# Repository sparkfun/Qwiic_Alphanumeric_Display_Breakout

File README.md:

SparkFun Qwiic Alphanumeric Display
========================================

[*Qwiic Alphanumeric Display - Pink (COM-16919)*](https://www.sparkfun.com/products/16919)

[*Qwiic Alphanumeric Display - Green (COM-18566)*](https://www.sparkfun.com/products/18566)

[*Qwiic Alphanumeric Display - Red (COM-16916)*](https://www.sparkfun.com/products/16916)

[*Qwiic Alphanumeric Display - Blue (COM-16917)*](https://www.sparkfun.com/products/16917)

[*Qwiic Alphanumeric Display - Purple (COM-16918)*](https://www.sparkfun.com/products/16918)

[*Qwiic Alphanumeric Display - White (COM-18565)*](https://www.sparkfun.com/products/18565)

We are quite familiar with seven-segment displays. We see them on our alarm clocks, ovens, and microwaves. By adding more segments to each digit you can display more than just numbers! Introducing the brand new SparkFun Qwiic Alphanumeric Display. These fourteen-segment digits allow you to display all sorts of numbers, characters, and symbols. With [Qwiic](https://www.sparkfun.com/qwiic), simply plug it in and go. No soldering, no figuring out which is SDA or SCL, and no voltage regulation or translation required! 

The [SparkFun Alphanumeric Display Arduino library](https://github.com/sparkfun/SparkFun_Alphanumeric_Display_Arduino_Library) makes printing strings to the display as easy as calling the print() function. With this library, you'll be able to send I<sup>2</sup>C commands to the VK16K33 LED driver chip to light up segments (including the decimal point or colon) and even scroll your string across the display. You can download the library through the Arduino library manager by searching 'SparkFun Alphanumeric Display' or you can get the GitHub repo as a .zip file and install the library from there.

The VK16K33 also supports I<sup>2</sup>C address configuration. Simply close a combination of the address jumpers on the back and you can communicate with up to four displays on the same bus. Our slim board design also features detachable standoff holes, vertical Qwiic connectors, and internal mounting holes.

SparkFun labored with love to design this board. Feel like supporting open source hardware? 
Buy a [board]() from SparkFun!

Repository Contents
-------------------

* **/Documents** - Data sheet for the LED Driver and Alphanumeric Displays (Blue and Red)
* **/Hardware** - Eagle design files (.brd, .sch)
* **/Production** - Production panel files (.brd) within the Production folder

Documentation
--------------
* **[Library](https://github.com/sparkfun/SparkFun_Alphanumeric_Display_Arduino_Library)** - <LANGUAGE> library for the Qwiic Alphanumeric Display Breakout.
* **[Hookup Guide](https://learn.sparkfun.com/tutorials/sparkfun-qwiic-alphanumeric-display-hookup-guide)** - Basic hookup guide for the Qwiic Alphanumeric Display Breakout.

License Information
-------------------

This product is _**open source**_! 

Please review the LICENSE.md file for license information. 

If you have any questions or concerns on licensing, please contact technical support on our [SparkFun forums](https://forum.sparkfun.com/viewforum.php?f=152).

Distributed as-is; no warranty is given.

- Your friends at SparkFun.

_<COLLABORATION CREDIT>_

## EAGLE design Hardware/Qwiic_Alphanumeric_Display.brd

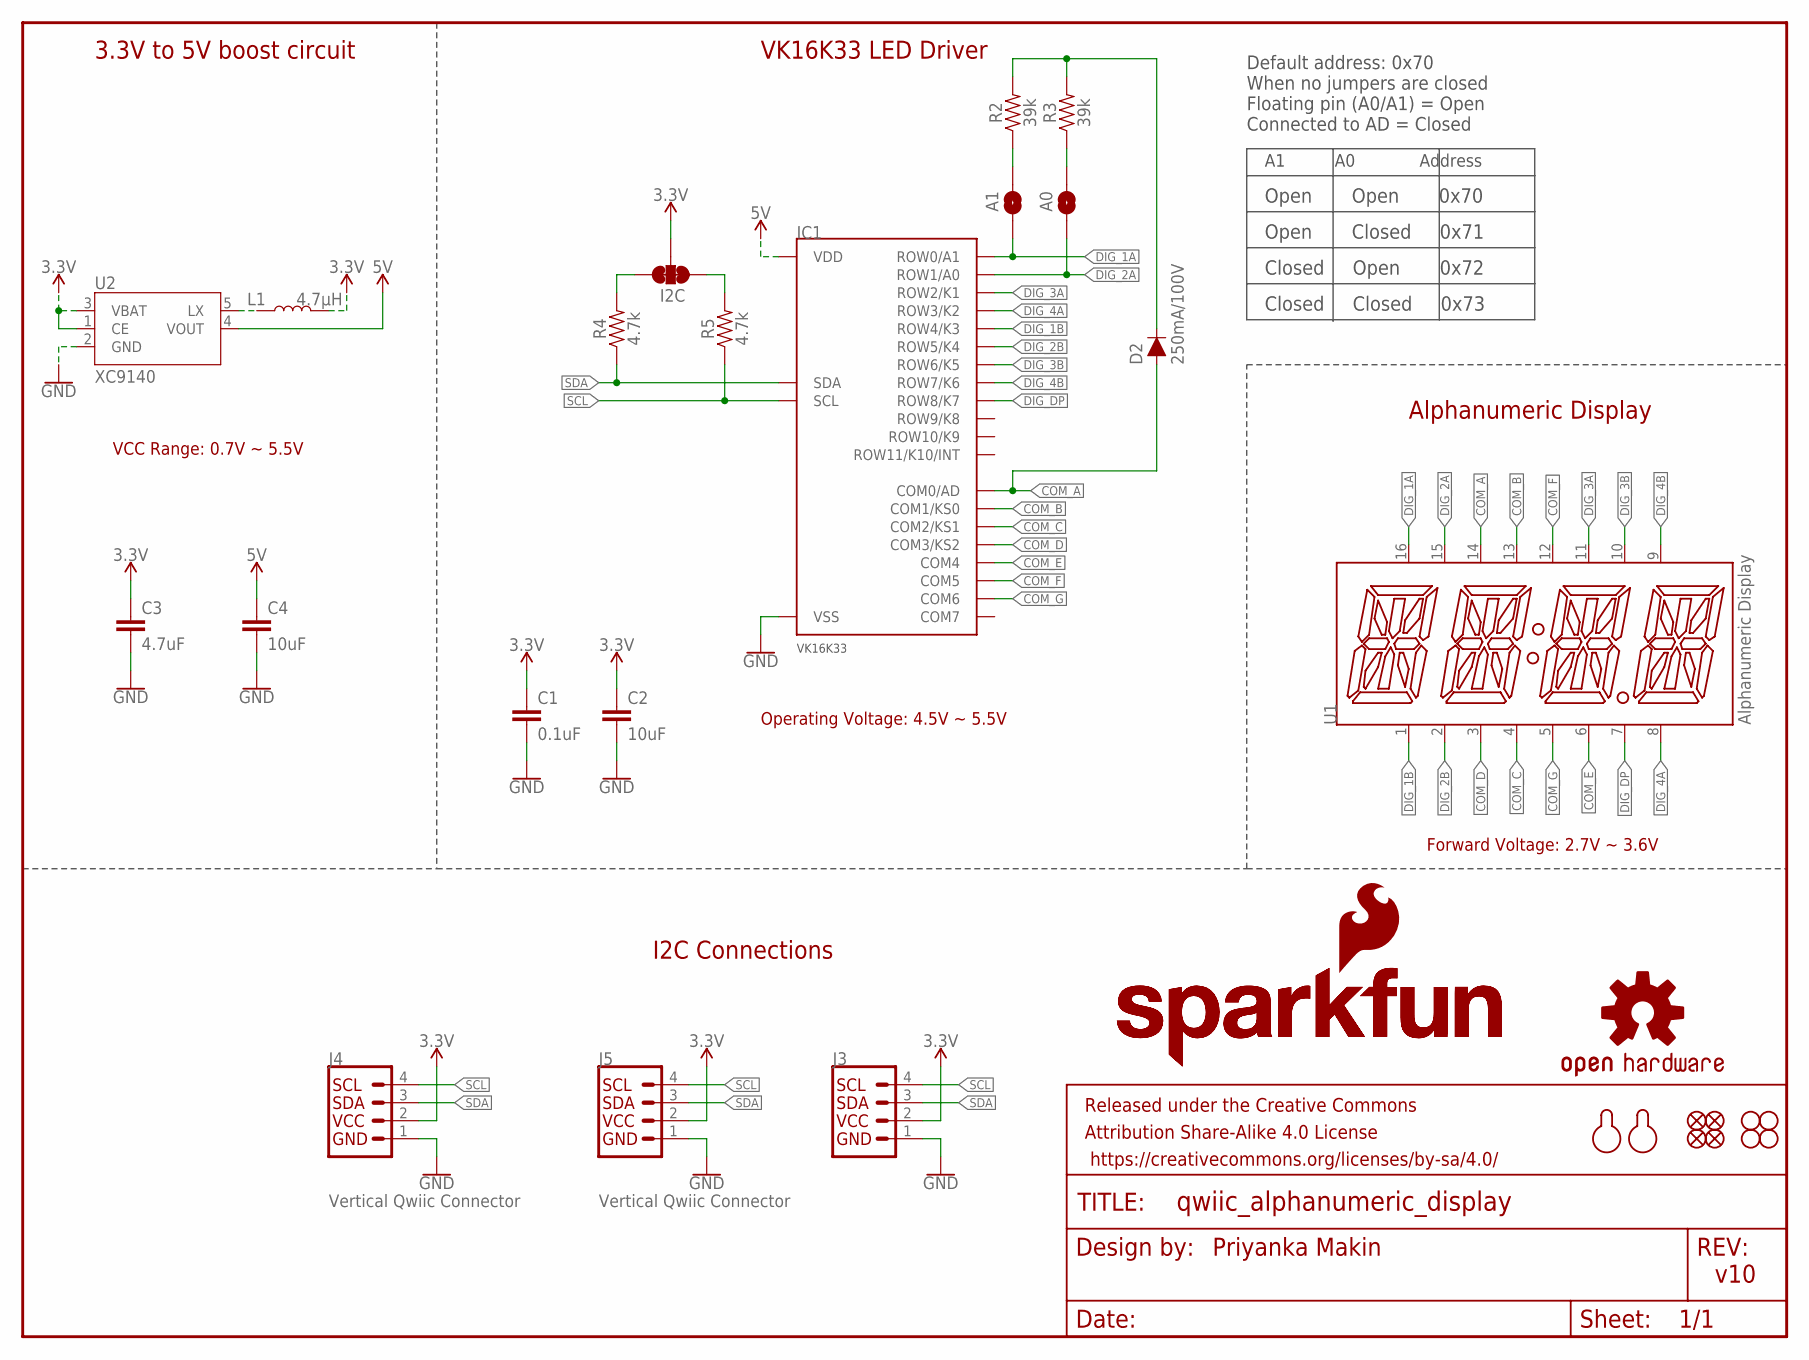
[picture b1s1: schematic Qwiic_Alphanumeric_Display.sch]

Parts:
A0, A1: JUMPER-SMT_2_NO_SILK; SMT-JUMPER_2_NO_SILK
C1: 0.1uF; 0603
C2, C4: 10uF; 0603
C3: 4.7uF; 0603
D2: 250mA/100V; SOD-323
FD1, FD2, FD3, FD4: FIDUCIAL1X2; FIDUCIAL-1X2
FRAME1: FRAME-LETTER; CREATIVE_COMMONS
H1, H2, H3, H4: STAND-OFF
I2C: JUMPER-SMT_3_2-NC_TRACE_NO-SILK; SMT-JUMPER_3_2-NC_TRACE_NO-SILK
IC1: VK16K33VK16K33; VK16K33
J3: I2C_STANDARD_NO_SILK; 1X04_NO_SILK
J4, J5: Vertical Qwiic Connector; JST04_1MM_VERT
L1: 4.7µH; INDUCTOR_4.7UH
LOGO1: OSHW-LOGOMINI; OSHW-LOGO-MINI
LOGO2, LOGO3: SFE_LOGO_NAME.1_INCH; SFE_LOGO_NAME_.1
LOGO4: SFE_LOGO_FLAME.1_INCH; SFE_LOGO_FLAME_.1
R2, R3: 39k; 0603
R4, R5: 4.7k; 0402-TIGHT
U1: Alphanumeric Display; SILSMART_DISPLAY
U2: XC9140; SOT23-5
U$3, U$7: MOUNTING_HOLE_M2-0.4X6

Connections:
3.3V: C1.1, C2.1, C3.1, I2C.2, J3.2, J4.2, J5.2, L1.P$2 (2), U2.1 (CE), U2.3 (VBAT)
5V: C4.1, IC1.24 (VDD), U2.4 (VOUT)
COM_A: D2.A, IC1.2 (COM0/AD), U1.14 (COM_A)
COM_B: IC1.3 (COM1/KS0), U1.13 (COM_B)
COM_C: IC1.4 (COM2/KS1), U1.4 (COM_C)
COM_D: IC1.5 (COM3/KS2), U1.3 (COM_D)
COM_E: IC1.6 (COM4), U1.6 (COM_E)
COM_F: IC1.7 (COM5), U1.12 (COM_F)
COM_G: IC1.8 (COM6), U1.5 (COM_G1)
DIG_1A: A1.1, IC1.21 (ROW0/A1), U1.16 (DIG_1A)
DIG_1B: IC1.17 (ROW4/K3), U1.1 (DIG_1B)
DIG_2A: A0.1, IC1.20 (ROW1/A0), U1.15 (DIG_2A)
DIG_2B: IC1.16 (ROW5/K4), U1.2 (DIG_2B)
DIG_3A: IC1.19 (ROW2/K1), U1.11 (DIG_3A)
DIG_3B: IC1.15 (ROW6/K5), U1.10 (DIG_3B)
DIG_4A: IC1.18 (ROW3/K2), U1.8 (DIG_4A)
DIG_4B: IC1.14 (ROW7/K6), U1.9 (DIG_4B)
DIG_DP: IC1.13 (ROW8/K7), U1.7 (DIG_DP)
GND: C1.2, C2.2, C3.2, C4.2, IC1.1 (VSS), J3.1, J4.1, J5.1, U2.2 (GND)
unnamed: I2C.3, R4.2
unnamed: A1.2, R2.1
unnamed: A0.2, R3.1
unnamed: I2C.1, R5.2
unnamed: D2.C, R2.2, R3.2
unnamed: L1.P$1 (1), U2.5 (LX)
SCL: IC1.22 (SCL), J3.4, J4.4, J5.4, R5.1
SDA: IC1.23 (SDA), J3.3, J4.3, J5.3, R4.1

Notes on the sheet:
Priyanka Makin
I2C Connections
A1 A0 Address
Default address: 0x70 When no jumpers are closed Floating pin (A0/A1) = Open Connected to AD = Closed
v10
Alphanumeric Display
VK16K33 LED Driver
3.3V to 5V boost circuit
VK16K33
VCC Range: 0.7V ~ 5.5V
Operating Voltage: 4.5V ~ 5.5V
Forward Voltage: 2.7V ~ 3.6V
Open Closed 0x71
Open Open 0x70
Closed Open 0x72
Closed Closed 0x73

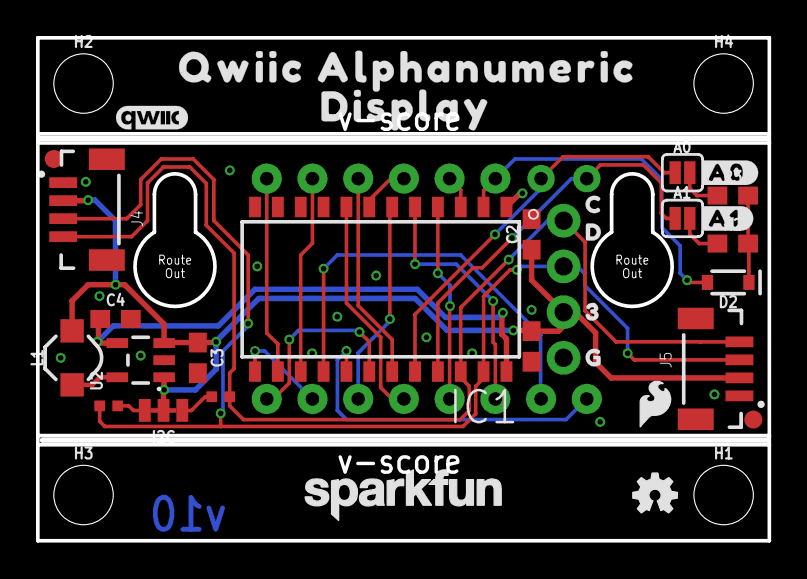
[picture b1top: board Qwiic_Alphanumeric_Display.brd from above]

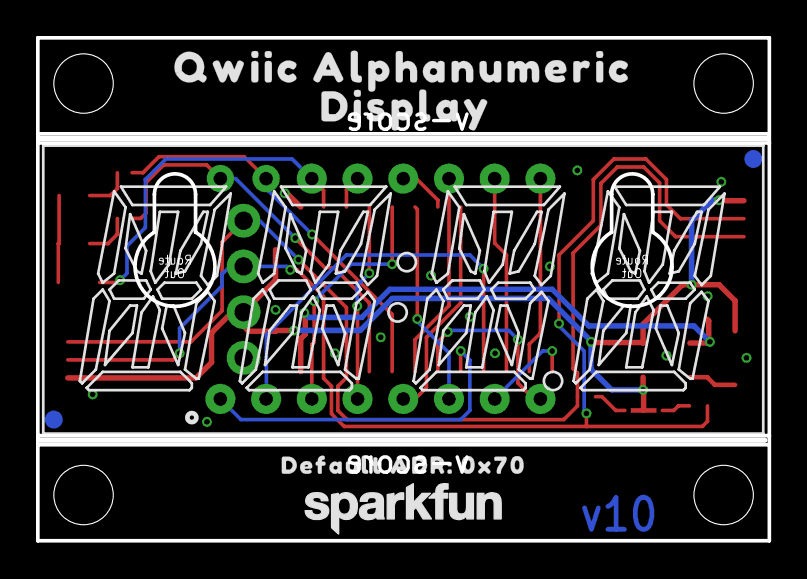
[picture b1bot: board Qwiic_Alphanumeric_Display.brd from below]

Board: 2 copper layers, 40.6 x 27.9 mm, 46 parts (7 on the bottom side), 27 nets.

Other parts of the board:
U$1: DEFAULT_ADR#_0X700
U$6: QWIIC_4MM
U$8, U$9: QWIIC_ALPHANUMERIC0
U$10, U$11: DISPLAY0
U$12: #A0#0
U$13: #A1#0
U$14: C0
U$15: D0
U$16: 30
U$17: G0

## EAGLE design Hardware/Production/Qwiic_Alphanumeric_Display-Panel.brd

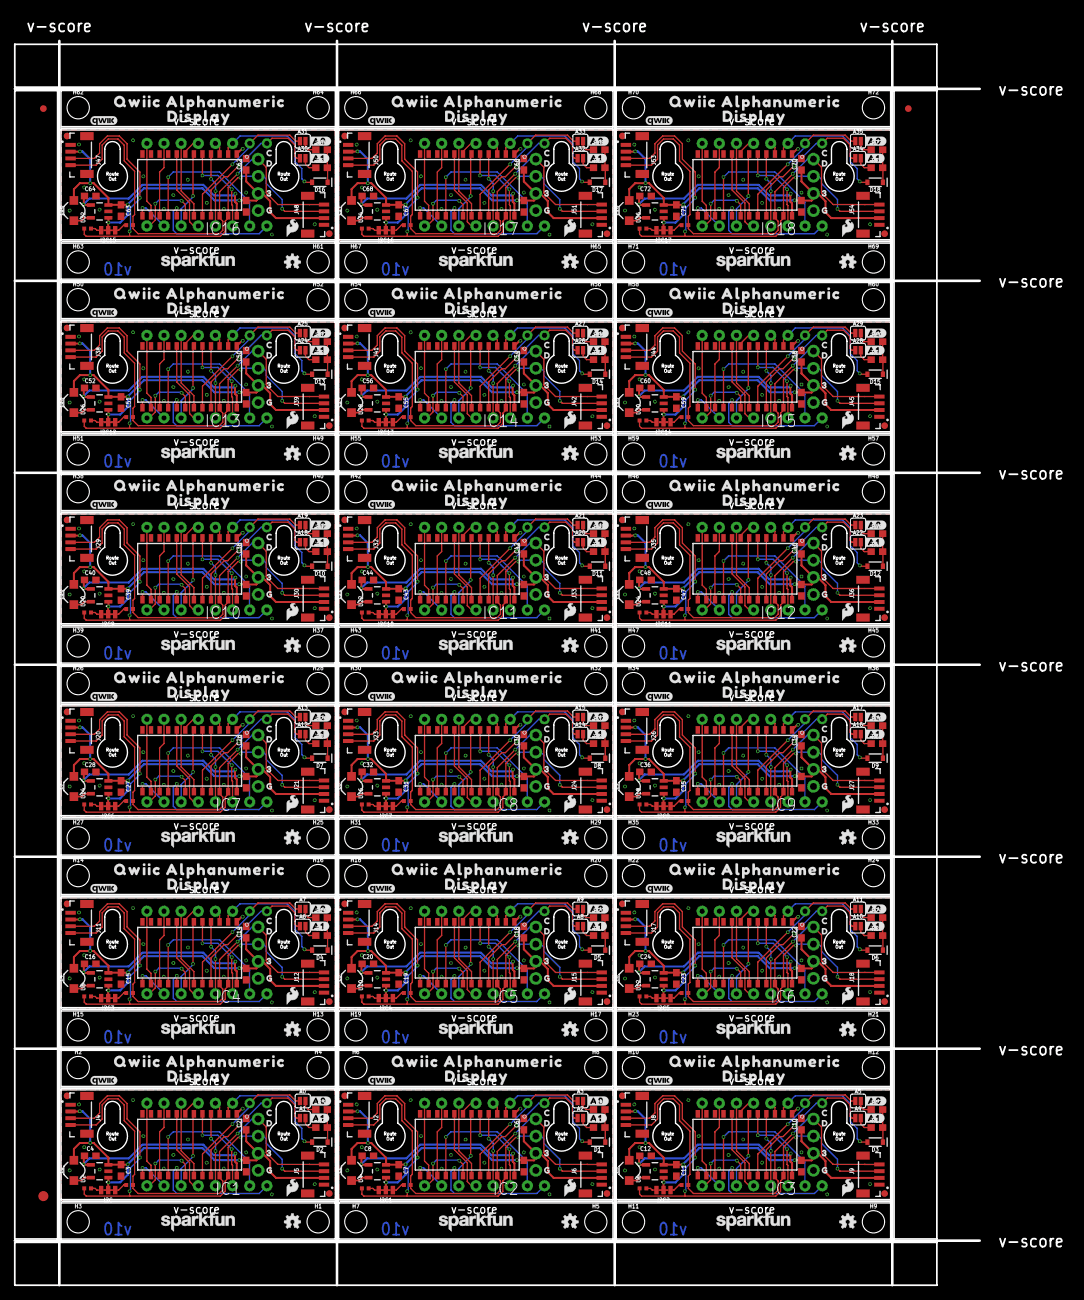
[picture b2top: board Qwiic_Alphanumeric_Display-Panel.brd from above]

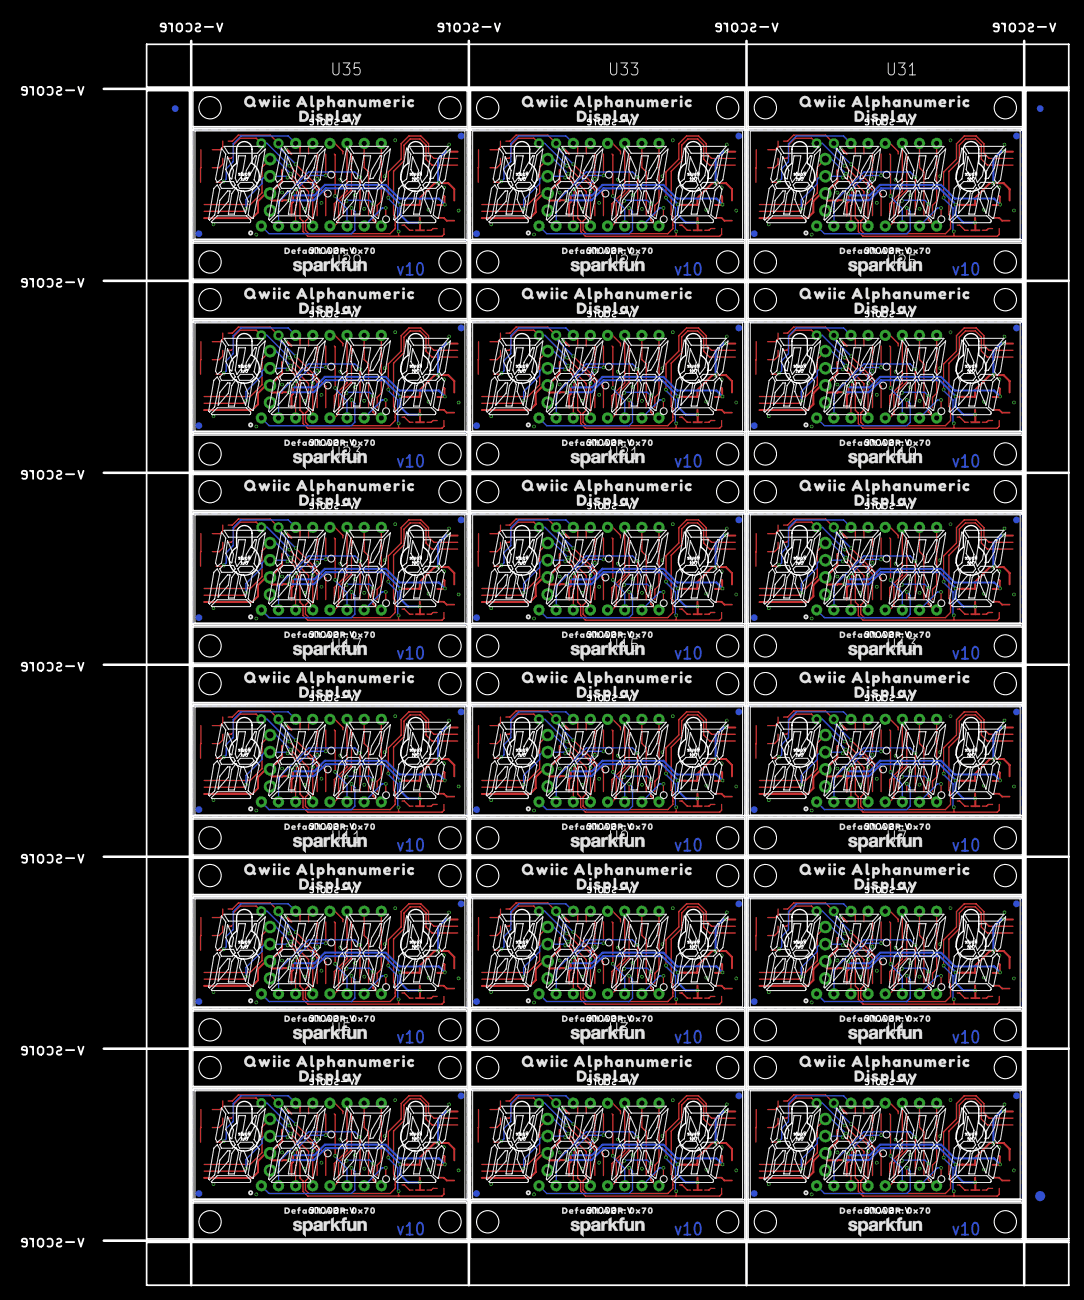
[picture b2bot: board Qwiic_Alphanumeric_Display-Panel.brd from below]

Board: 2 copper layers, 143.0 x 184.4 mm, 816 parts (129 on the bottom side), 486 nets.

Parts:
A0, A1, A2, A3, A4, A5, A6, A7, A8, A9, A10, A11, A12, A13, A14, A15, A16, A17, A18, A19, A20, A21, A22, A23, A24, A25, A26, A27, A28, A29, A30, A31, A32, A33, A34, A35: JUMPER-SMT_2_NO_SILK; SMT-JUMPER_2_NO_SILK
C1, C5, C9, C13, C17, C21, C25, C29, C33, C37, C41, C45, C49, C53, C57, C61, C65, C69: 0.1uF; 0603
C2, C4, C6, C8, C10, C12, C14, C16, C18, C20, C22, C24, C26, C28, C30, C32, C34, C36, C38, C40, C42, C44, C46, C48, C50, C52, C54, C56, C58, C60, C62, C64, C66, C68, C70, C72: 10uF; 0603
C3, C7, C11, C15, C19, C23, C27, C31, C35, C39, C43, C47, C51, C55, C59, C63, C67, C71: 4.7uF; 0603
D1, D2, D3, D4, D5, D6, D7, D8, D9, D10, D11, D12, D13, D14, D15, D16, D17, D18: 250mA/100V; SOD-323
E$1, E$2, E$3, E$4: FIDUCIAL-1X2
E$5, E$6: FIDUCIAL-1.5X3
FD1, FD2, FD3, FD4, FD5, FD6, FD7, FD8, FD9, FD10, FD11, FD12, FD13, FD14, FD15, FD16, FD17, FD18, FD19, FD20, FD21, FD22, FD23, FD24, FD25, FD26, FD27, FD28, FD29, FD30, FD31, FD32, FD33, FD34, FD35, FD36, FD37, FD38, FD39, FD40, FD41, FD42, FD43, FD44, FD45, FD46, FD47, FD48, FD49, FD50, FD51, FD52, FD53, FD54, FD55, FD56, FD57, FD58, FD59, FD60, FD61, FD62, FD63, FD64, FD65, FD66, FD67, FD68, FD69, FD70, FD71, FD72: FIDUCIAL1X2; FIDUCIAL-1X2
H1, H2, H3, H4, H5, H6, H7, H8, H9, H10, H11, H12, H13, H14, H15, H16, H17, H18, H19, H20, H21, H22, H23, H24, H25, H26, H27, H28, H29, H30, H31, H32, H33, H34, H35, H36, H37, H38, H39, H40, H41, H42, H43, H44, H45, H46, H47, H48, H49, H50, H51, H52, H53, H54, H55, H56, H57, H58, H59, H60, H61, H62, H63, H64, H65, H66, H67, H68, H69, H70, H71, H72: STAND-OFF
I2C, I2C1, I2C2, I2C3, I2C4, I2C5, I2C6, I2C7, I2C8, I2C9, I2C10, I2C11, I2C12, I2C13, I2C14, I2C15, I2C16, I2C17: JUMPER-SMT_3_2-NC_TRACE_NO-SILK; SMT-JUMPER_3_2-NC_TRACE_NO-SILK
IC1, IC2, IC3, IC4, IC5, IC6, IC7, IC8, IC9, IC10, IC11, IC12, IC13, IC14, IC15, IC16, IC17, IC18: VK16K33
J1, J3, J7, J10, J13, J16, J19, J22, J25, J28, J31, J34, J37, J40, J43, J46, J49, J52: 1X04_NO_SILK
J2, J4, J5, J6, J8, J9, J11, J12, J14, J15, J17, J18, J20, J21, J23, J24, J26, J27, J29, J30, J32, J33, J35, J36, J38, J39, J41, J42, J44, J45, J47, J48, J50, J51, J53, J54: Vertical Qwiic Connector; JST04_1MM_VERT
L1, L2, L3, L4, L5, L6, L7, L8, L9, L10, L11, L12, L13, L14, L15, L16, L17, L18: 4.7µH; INDUCTOR_4.7UH
LOGO1, LOGO5, LOGO9, LOGO13, LOGO17, LOGO21, LOGO25, LOGO29, LOGO33, LOGO37, LOGO41, LOGO45, LOGO49, LOGO53, LOGO57, LOGO61, LOGO65, LOGO69: OSHW-LOGOMINI; OSHW-LOGO-MINI
LOGO2, LOGO3, LOGO6, LOGO7, LOGO10, LOGO11, LOGO14, LOGO15, LOGO18, LOGO19, LOGO22, LOGO23, LOGO26, LOGO27, LOGO30, LOGO31, LOGO34, LOGO35, LOGO38, LOGO39, LOGO42, LOGO43, LOGO46, LOGO47, LOGO50, LOGO51, LOGO54, LOGO55, LOGO58, LOGO59, LOGO62, LOGO63, LOGO66, LOGO67, LOGO70, LOGO71: SFE_LOGO_NAME.1_INCH; SFE_LOGO_NAME_.1
LOGO4, LOGO8, LOGO12, LOGO16, LOGO20, LOGO24, LOGO28, LOGO32, LOGO36, LOGO40, LOGO44, LOGO48, LOGO52, LOGO56, LOGO60, LOGO64, LOGO68, LOGO72: SFE_LOGO_FLAME.1_INCH; SFE_LOGO_FLAME_.1
R1, R4, R5, R6, R9, R10, R13, R14, R17, R18, R21, R22, R25, R26, R29, R30, R33, R34, R37, R38, R41, R42, R45, R46, R49, R50, R53, R54, R57, R58, R61, R62, R65, R66, R69, R70: 4.7k; 0402-TIGHT
R2, R3, R7, R8, R11, R12, R15, R16, R19, R20, R23, R24, R27, R28, R31, R32, R35, R36, R39, R40, R43, R44, R47, R48, R51, R52, R55, R56, R59, R60, R63, R64, R67, R68, R71, R72: 39k; 0603
U1, U3, U5, U7, U9, U11, U13, U15, U17, U19, U21, U23, U25, U27, U29, U31, U33, U35: Alphanumeric Display; SILSMART_DISPLAY
U2, U4, U6, U8, U10, U12, U14, U16, U18, U20, U22, U24, U26, U28, U30, U32, U34, U36: XC9140; SOT23-5
U$1, U$28, U$42, U$56, U$70, U$84, U$98, U$112, U$126, U$140, U$154, U$168, U$182, U$196, U$210, U$224, U$238, U$252: DEFAULT_ADR#_0X700
U$2, U$6, U$29, U$43, U$57, U$71, U$85, U$99, U$113, U$127, U$141, U$155, U$169, U$183, U$197, U$211, U$225, U$239: QWIIC_4MM
U$3, U$4, U$5, U$7, U$30, U$31, U$44, U$45, U$58, U$59, U$72, U$73, U$86, U$87, U$100, U$101, U$114, U$115, U$128, U$129, U$142, U$143, U$156, U$157, U$170, U$171, U$184, U$185, U$198, U$199, U$212, U$213, U$226, U$227, U$240, U$241: MOUNTING_HOLE_M2-0.4X6
U$8, U$9, U$18, U$19, U$32, U$33, U$46, U$47, U$60, U$61, U$74, U$75, U$88, U$89, U$102, U$103, U$116, U$117, U$130, U$131, U$144, U$145, U$158, U$159, U$172, U$173, U$186, U$187, U$200, U$201, U$214, U$215, U$228, U$229, U$242, U$243: QWIIC_ALPHANUMERIC0
U$10, U$11, U$20, U$21, U$34, U$35, U$48, U$49, U$62, U$63, U$76, U$77, U$90, U$91, U$104, U$105, U$118, U$119, U$132, U$133, U$146, U$147, U$160, U$161, U$174, U$175, U$188, U$189, U$202, U$203, U$216, U$217, U$230, U$231, U$244, U$245: DISPLAY0
U$12, U$22, U$36, U$50, U$64, U$78, U$92, U$106, U$120, U$134, U$148, U$162, U$176, U$190, U$204, U$218, U$232, U$246: #A0#0
U$13, U$23, U$37, U$51, U$65, U$79, U$93, U$107, U$121, U$135, U$149, U$163, U$177, U$191, U$205, U$219, U$233, U$247: #A1#0
U$14, U$24, U$38, U$52, U$66, U$80, U$94, U$108, U$122, U$136, U$150, U$164, U$178, U$192, U$206, U$220, U$234, U$248: C0
U$15, U$25, U$39, U$53, U$67, U$81, U$95, U$109, U$123, U$137, U$151, U$165, U$179, U$193, U$207, U$221, U$235, U$249: D0
U$16, U$26, U$40, U$54, U$68, U$82, U$96, U$110, U$124, U$138, U$152, U$166, U$180, U$194, U$208, U$222, U$236, U$250: 30
U$17, U$27, U$41, U$55, U$69, U$83, U$97, U$111, U$125, U$139, U$153, U$167, U$181, U$195, U$209, U$223, U$237, U$251: G0

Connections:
3.3V: C1.1, C2.1, C3.1, I2C.2, J3.2, J4.2, J5.2, L1.P$2, U2.1, U2.3
3.3V1: C5.1, C6.1, C7.1, I2C1.2, J1.2, J2.2, J6.2, L2.P$2, U4.1, U4.3
3.3V2: C9.1, C10.1, C11.1, I2C2.2, J7.2, J8.2, J9.2, L3.P$2, U6.1, U6.3
3.3V3: C13.1, C14.1, C15.1, I2C3.2, J10.2, J11.2, J12.2, L4.P$2, U8.1, U8.3
3.3V4: C17.1, C18.1, C19.1, I2C4.2, J13.2, J14.2, J15.2, L5.P$2, U10.1, U10.3
3.3V5: C21.1, C22.1, C23.1, I2C5.2, J16.2, J17.2, J18.2, L6.P$2, U12.1, U12.3
3.3V6: C25.1, C26.1, C27.1, I2C6.2, J19.2, J20.2, J21.2, L7.P$2, U14.1, U14.3
3.3V7: C29.1, C30.1, C31.1, I2C7.2, J22.2, J23.2, J24.2, L8.P$2, U16.1, U16.3
3.3V8: C33.1, C34.1, C35.1, I2C8.2, J25.2, J26.2, J27.2, L9.P$2, U18.1, U18.3
3.3V9: C37.1, C38.1, C39.1, I2C9.2, J28.2, J29.2, J30.2, L10.P$2, U20.1, U20.3
3.3V10: C41.1, C42.1, C43.1, I2C10.2, J31.2, J32.2, J33.2, L11.P$2, U22.1, U22.3
3.3V11: C45.1, C46.1, C47.1, I2C11.2, J34.2, J35.2, J36.2, L12.P$2, U24.1, U24.3
3.3V12: C49.1, C50.1, C51.1, I2C12.2, J37.2, J38.2, J39.2, L13.P$2, U26.1, U26.3
3.3V13: C53.1, C54.1, C55.1, I2C13.2, J40.2, J41.2, J42.2, L14.P$2, U28.1, U28.3
3.3V14: C57.1, C58.1, C59.1, I2C14.2, J43.2, J44.2, J45.2, L15.P$2, U30.1, U30.3
3.3V15: C61.1, C62.1, C63.1, I2C15.2, J46.2, J47.2, J48.2, L16.P$2, U32.1, U32.3
3.3V16: C65.1, C66.1, C67.1, I2C16.2, J49.2, J50.2, J51.2, L17.P$2, U34.1, U34.3
3.3V17: C69.1, C70.1, C71.1, I2C17.2, J52.2, J53.2, J54.2, L18.P$2, U36.1, U36.3
5V: C4.1, IC1.24, U2.4
5V1: C8.1, IC2.24, U4.4
5V2: C12.1, IC3.24, U6.4
5V3: C16.1, IC4.24, U8.4
5V4: C20.1, IC5.24, U10.4
5V5: C24.1, IC6.24, U12.4
5V6: C28.1, IC7.24, U14.4
5V7: C32.1, IC8.24, U16.4
5V8: C36.1, IC9.24, U18.4
5V9: C40.1, IC10.24, U20.4
5V10: C44.1, IC11.24, U22.4
5V11: C48.1, IC12.24, U24.4
5V12: C52.1, IC13.24, U26.4
5V13: C56.1, IC14.24, U28.4
5V14: C60.1, IC15.24, U30.4
5V15: C64.1, IC16.24, U32.4
5V16: C68.1, IC17.24, U34.4
5V17: C72.1, IC18.24, U36.4
COM_A: D2.A, IC1.2, U1.14
COM_A1: D1.A, IC2.2, U3.14
COM_A2: D3.A, IC3.2, U5.14
COM_A3: D4.A, IC4.2, U7.14
COM_A4: D5.A, IC5.2, U9.14
COM_A5: D6.A, IC6.2, U11.14
COM_A6: D7.A, IC7.2, U13.14
COM_A7: D8.A, IC8.2, U15.14
COM_A8: D9.A, IC9.2, U17.14
COM_A9: D10.A, IC10.2, U19.14
COM_A10: D11.A, IC11.2, U21.14
COM_A11: D12.A, IC12.2, U23.14
COM_A12: D13.A, IC13.2, U25.14
COM_A13: D14.A, IC14.2, U27.14
COM_A14: D15.A, IC15.2, U29.14
COM_A15: D16.A, IC16.2, U31.14
COM_A16: D17.A, IC17.2, U33.14
COM_A17: D18.A, IC18.2, U35.14
COM_B: IC1.3, U1.13
COM_B1: IC2.3, U3.13
COM_B2: IC3.3, U5.13
COM_B3: IC4.3, U7.13
COM_B4: IC5.3, U9.13
COM_B5: IC6.3, U11.13
COM_B6: IC7.3, U13.13
COM_B7: IC8.3, U15.13
COM_B8: IC9.3, U17.13
COM_B9: IC10.3, U19.13
COM_B10: IC11.3, U21.13
COM_B11: IC12.3, U23.13
COM_B12: IC13.3, U25.13
COM_B13: IC14.3, U27.13
COM_B14: IC15.3, U29.13
COM_B15: IC16.3, U31.13
COM_B16: IC17.3, U33.13
COM_B17: IC18.3, U35.13
COM_C: IC1.4, U1.4
COM_C1: IC2.4, U3.4
COM_C2: IC3.4, U5.4
COM_C3: IC4.4, U7.4
COM_C4: IC5.4, U9.4
COM_C5: IC6.4, U11.4
COM_C6: IC7.4, U13.4
COM_C7: IC8.4, U15.4
COM_C8: IC9.4, U17.4
COM_C9: IC10.4, U19.4
COM_C10: IC11.4, U21.4
COM_C11: IC12.4, U23.4
COM_C12: IC13.4, U25.4
COM_C13: IC14.4, U27.4
COM_C14: IC15.4, U29.4
COM_C15: IC16.4, U31.4
COM_C16: IC17.4, U33.4
COM_C17: IC18.4, U35.4
COM_D: IC1.5, U1.3
COM_D1: IC2.5, U3.3
COM_D2: IC3.5, U5.3
COM_D3: IC4.5, U7.3
COM_D4: IC5.5, U9.3
COM_D5: IC6.5, U11.3
COM_D6: IC7.5, U13.3
COM_D7: IC8.5, U15.3
COM_D8: IC9.5, U17.3
COM_D9: IC10.5, U19.3
COM_D10: IC11.5, U21.3
COM_D11: IC12.5, U23.3
COM_D12: IC13.5, U25.3
COM_D13: IC14.5, U27.3
COM_D14: IC15.5, U29.3
COM_D15: IC16.5, U31.3
COM_D16: IC17.5, U33.3
COM_D17: IC18.5, U35.3
COM_E: IC1.6, U1.6
COM_E1: IC2.6, U3.6
COM_E2: IC3.6, U5.6
COM_E3: IC4.6, U7.6
COM_E4: IC5.6, U9.6
COM_E5: IC6.6, U11.6
COM_E6: IC7.6, U13.6
COM_E7: IC8.6, U15.6
COM_E8: IC9.6, U17.6
COM_E9: IC10.6, U19.6
COM_E10: IC11.6, U21.6
COM_E11: IC12.6, U23.6
COM_E12: IC13.6, U25.6
COM_E13: IC14.6, U27.6
COM_E14: IC15.6, U29.6
COM_E15: IC16.6, U31.6
COM_E16: IC17.6, U33.6
COM_E17: IC18.6, U35.6
COM_F: IC1.7, U1.12
COM_F1: IC2.7, U3.12
COM_F2: IC3.7, U5.12
COM_F3: IC4.7, U7.12
COM_F4: IC5.7, U9.12
COM_F5: IC6.7, U11.12
COM_F6: IC7.7, U13.12
COM_F7: IC8.7, U15.12
COM_F8: IC9.7, U17.12
COM_F9: IC10.7, U19.12
COM_F10: IC11.7, U21.12
COM_F11: IC12.7, U23.12
COM_F12: IC13.7, U25.12
COM_F13: IC14.7, U27.12
COM_F14: IC15.7, U29.12
COM_F15: IC16.7, U31.12
COM_F16: IC17.7, U33.12
COM_F17: IC18.7, U35.12
COM_G: IC1.8, U1.5
COM_G1: IC2.8, U3.5
COM_G2: IC3.8, U5.5
COM_G3: IC4.8, U7.5
COM_G4: IC5.8, U9.5
COM_G5: IC6.8, U11.5
COM_G6: IC7.8, U13.5
COM_G7: IC8.8, U15.5
COM_G8: IC9.8, U17.5
COM_G9: IC10.8, U19.5
COM_G10: IC11.8, U21.5
COM_G11: IC12.8, U23.5
COM_G12: IC13.8, U25.5
COM_G13: IC14.8, U27.5
COM_G14: IC15.8, U29.5
COM_G15: IC16.8, U31.5
COM_G16: IC17.8, U33.5
COM_G17: IC18.8, U35.5
DIG_1A: A1.1, IC1.21, U1.16
DIG_1A1: A2.1, IC2.21, U3.16
DIG_1A2: A4.1, IC3.21, U5.16
DIG_1A3: A6.1, IC4.21, U7.16
DIG_1A4: A8.1, IC5.21, U9.16
DIG_1A5: A10.1, IC6.21, U11.16
DIG_1A6: A12.1, IC7.21, U13.16
DIG_1A7: A14.1, IC8.21, U15.16
DIG_1A8: A16.1, IC9.21, U17.16
DIG_1A9: A18.1, IC10.21, U19.16
DIG_1A10: A20.1, IC11.21, U21.16
DIG_1A11: A22.1, IC12.21, U23.16
DIG_1A12: A24.1, IC13.21, U25.16
DIG_1A13: A26.1, IC14.21, U27.16
DIG_1A14: A28.1, IC15.21, U29.16
DIG_1A15: A30.1, IC16.21, U31.16
DIG_1A16: A32.1, IC17.21, U33.16
DIG_1A17: A34.1, IC18.21, U35.16
DIG_1B: IC1.17, U1.1
DIG_1B1: IC2.17, U3.1
DIG_1B2: IC3.17, U5.1
DIG_1B3: IC4.17, U7.1
DIG_1B4: IC5.17, U9.1
DIG_1B5: IC6.17, U11.1
DIG_1B6: IC7.17, U13.1
DIG_1B7: IC8.17, U15.1
DIG_1B8: IC9.17, U17.1
DIG_1B9: IC10.17, U19.1
DIG_1B10: IC11.17, U21.1
DIG_1B11: IC12.17, U23.1
DIG_1B12: IC13.17, U25.1
DIG_1B13: IC14.17, U27.1
DIG_1B14: IC15.17, U29.1
DIG_1B15: IC16.17, U31.1
DIG_1B16: IC17.17, U33.1
DIG_1B17: IC18.17, U35.1
DIG_2A: A0.1, IC1.20, U1.15
DIG_2A1: A3.1, IC2.20, U3.15
DIG_2A2: A5.1, IC3.20, U5.15
DIG_2A3: A7.1, IC4.20, U7.15
DIG_2A4: A9.1, IC5.20, U9.15
DIG_2A5: A11.1, IC6.20, U11.15
DIG_2A6: A13.1, IC7.20, U13.15
DIG_2A7: A15.1, IC8.20, U15.15
DIG_2A8: A17.1, IC9.20, U17.15
DIG_2A9: A19.1, IC10.20, U19.15
DIG_2A10: A21.1, IC11.20, U21.15
DIG_2A11: A23.1, IC12.20, U23.15
DIG_2A12: A25.1, IC13.20, U25.15
DIG_2A13: A27.1, IC14.20, U27.15
DIG_2A14: A29.1, IC15.20, U29.15
DIG_2A15: A31.1, IC16.20, U31.15
DIG_2A16: A33.1, IC17.20, U33.15
DIG_2A17: A35.1, IC18.20, U35.15
DIG_2B: IC1.16, U1.2
DIG_2B1: IC2.16, U3.2
DIG_2B2: IC3.16, U5.2
DIG_2B3: IC4.16, U7.2
DIG_2B4: IC5.16, U9.2
DIG_2B5: IC6.16, U11.2
DIG_2B6: IC7.16, U13.2
DIG_2B7: IC8.16, U15.2
DIG_2B8: IC9.16, U17.2
DIG_2B9: IC10.16, U19.2
DIG_2B10: IC11.16, U21.2
DIG_2B11: IC12.16, U23.2
DIG_2B12: IC13.16, U25.2
DIG_2B13: IC14.16, U27.2
DIG_2B14: IC15.16, U29.2
DIG_2B15: IC16.16, U31.2
DIG_2B16: IC17.16, U33.2
DIG_2B17: IC18.16, U35.2
DIG_3A: IC1.19, U1.11
DIG_3A1: IC2.19, U3.11
DIG_3A2: IC3.19, U5.11
DIG_3A3: IC4.19, U7.11
DIG_3A4: IC5.19, U9.11
DIG_3A5: IC6.19, U11.11
DIG_3A6: IC7.19, U13.11
DIG_3A7: IC8.19, U15.11
DIG_3A8: IC9.19, U17.11
DIG_3A9: IC10.19, U19.11
DIG_3A10: IC11.19, U21.11
DIG_3A11: IC12.19, U23.11
DIG_3A12: IC13.19, U25.11
DIG_3A13: IC14.19, U27.11
DIG_3A14: IC15.19, U29.11
DIG_3A15: IC16.19, U31.11
DIG_3A16: IC17.19, U33.11
DIG_3A17: IC18.19, U35.11
DIG_3B: IC1.15, U1.10
DIG_3B1: IC2.15, U3.10
DIG_3B2: IC3.15, U5.10
DIG_3B3: IC4.15, U7.10
DIG_3B4: IC5.15, U9.10
DIG_3B5: IC6.15, U11.10
DIG_3B6: IC7.15, U13.10
DIG_3B7: IC8.15, U15.10
DIG_3B8: IC9.15, U17.10
DIG_3B9: IC10.15, U19.10
DIG_3B10: IC11.15, U21.10
DIG_3B11: IC12.15, U23.10
DIG_3B12: IC13.15, U25.10
DIG_3B13: IC14.15, U27.10
DIG_3B14: IC15.15, U29.10
DIG_3B15: IC16.15, U31.10
DIG_3B16: IC17.15, U33.10
DIG_3B17: IC18.15, U35.10
DIG_4A: IC1.18, U1.8
DIG_4A1: IC2.18, U3.8
DIG_4A2: IC3.18, U5.8
DIG_4A3: IC4.18, U7.8
DIG_4A4: IC5.18, U9.8
DIG_4A5: IC6.18, U11.8
DIG_4A6: IC7.18, U13.8
DIG_4A7: IC8.18, U15.8
DIG_4A8: IC9.18, U17.8
DIG_4A9: IC10.18, U19.8
DIG_4A10: IC11.18, U21.8
DIG_4A11: IC12.18, U23.8
DIG_4A12: IC13.18, U25.8
DIG_4A13: IC14.18, U27.8
DIG_4A14: IC15.18, U29.8
DIG_4A15: IC16.18, U31.8
DIG_4A16: IC17.18, U33.8
DIG_4A17: IC18.18, U35.8
DIG_4B: IC1.14, U1.9
DIG_4B1: IC2.14, U3.9
DIG_4B2: IC3.14, U5.9
DIG_4B3: IC4.14, U7.9
DIG_4B4: IC5.14, U9.9
DIG_4B5: IC6.14, U11.9
DIG_4B6: IC7.14, U13.9
DIG_4B7: IC8.14, U15.9
DIG_4B8: IC9.14, U17.9
DIG_4B9: IC10.14, U19.9
DIG_4B10: IC11.14, U21.9
DIG_4B11: IC12.14, U23.9
DIG_4B12: IC13.14, U25.9
DIG_4B13: IC14.14, U27.9
DIG_4B14: IC15.14, U29.9
DIG_4B15: IC16.14, U31.9
DIG_4B16: IC17.14, U33.9
DIG_4B17: IC18.14, U35.9
DIG_DP: IC1.13, U1.7
DIG_DP1: IC2.13, U3.7
DIG_DP2: IC3.13, U5.7
DIG_DP3: IC4.13, U7.7
DIG_DP4: IC5.13, U9.7
DIG_DP5: IC6.13, U11.7
DIG_DP6: IC7.13, U13.7
DIG_DP7: IC8.13, U15.7
DIG_DP8: IC9.13, U17.7
DIG_DP9: IC10.13, U19.7
DIG_DP10: IC11.13, U21.7
DIG_DP11: IC12.13, U23.7
DIG_DP12: IC13.13, U25.7
DIG_DP13: IC14.13, U27.7
DIG_DP14: IC15.13, U29.7
DIG_DP15: IC16.13, U31.7
DIG_DP16: IC17.13, U33.7
DIG_DP17: IC18.13, U35.7
GND: C1.2, C2.2, C3.2, C4.2, IC1.1, J3.1, J4.1, J5.1, U2.2
GND1: C5.2, C6.2, C7.2, C8.2, IC2.1, J1.1, J2.1, J6.1, U4.2
GND2: C9.2, C10.2, C11.2, C12.2, IC3.1, J7.1, J8.1, J9.1, U6.2
GND3: C13.2, C14.2, C15.2, C16.2, IC4.1, J10.1, J11.1, J12.1, U8.2
GND4: C17.2, C18.2, C19.2, C20.2, IC5.1, J13.1, J14.1, J15.1, U10.2
GND5: C21.2, C22.2, C23.2, C24.2, IC6.1, J16.1, J17.1, J18.1, U12.2
GND6: C25.2, C26.2, C27.2, C28.2, IC7.1, J19.1, J20.1, J21.1, U14.2
GND7: C29.2, C30.2, C31.2, C32.2, IC8.1, J22.1, J23.1, J24.1, U16.2
GND8: C33.2, C34.2, C35.2, C36.2, IC9.1, J25.1, J26.1, J27.1, U18.2
GND9: C37.2, C38.2, C39.2, C40.2, IC10.1, J28.1, J29.1, J30.1, U20.2
GND10: C41.2, C42.2, C43.2, C44.2, IC11.1, J31.1, J32.1, J33.1, U22.2
GND11: C45.2, C46.2, C47.2, C48.2, IC12.1, J34.1, J35.1, J36.1, U24.2
GND12: C49.2, C50.2, C51.2, C52.2, IC13.1, J37.1, J38.1, J39.1, U26.2
GND13: C53.2, C54.2, C55.2, C56.2, IC14.1, J40.1, J41.1, J42.1, U28.2
GND14: C57.2, C58.2, C59.2, C60.2, IC15.1, J43.1, J44.1, J45.1, U30.2
GND15: C61.2, C62.2, C63.2, C64.2, IC16.1, J46.1, J47.1, J48.1, U32.2
GND16: C65.2, C66.2, C67.2, C68.2, IC17.1, J49.1, J50.1, J51.1, U34.2
GND17: C69.2, C70.2, C71.2, C72.2, IC18.1, J52.1, J53.1, J54.1, U36.2
unnamed: I2C.3, R4.2
unnamed: A1.2, R2.1
unnamed: A0.2, R3.1
unnamed: I2C.1, R5.2
unnamed: A2.2, R7.1
unnamed: D2.C, R2.2, R3.2
unnamed: A3.2, R8.1
unnamed: D1.C, R7.2, R8.2
unnamed: L2.P$1, U4.5
unnamed: L1.P$1, U2.5
unnamed: I2C1.3, R1.2
unnamed: I2C1.1, R6.2
unnamed: A4.2, R11.1
unnamed: A5.2, R12.1
unnamed: D3.C, R11.2, R12.2
unnamed: L3.P$1, U6.5
unnamed: I2C2.3, R9.2
unnamed: I2C2.1, R10.2
unnamed: A6.2, R15.1
unnamed: A7.2, R16.1
unnamed: D4.C, R15.2, R16.2
unnamed: L4.P$1, U8.5
unnamed: I2C3.3, R13.2
unnamed: I2C3.1, R14.2
unnamed: A8.2, R19.1
unnamed: A9.2, R20.1
unnamed: D5.C, R19.2, R20.2
unnamed: L5.P$1, U10.5
unnamed: I2C4.3, R17.2
unnamed: I2C4.1, R18.2
unnamed: A10.2, R23.1
unnamed: A11.2, R24.1
unnamed: D6.C, R23.2, R24.2
unnamed: L6.P$1, U12.5
unnamed: I2C5.3, R21.2
unnamed: I2C5.1, R22.2
unnamed: A12.2, R27.1
unnamed: A13.2, R28.1
unnamed: D7.C, R27.2, R28.2
unnamed: L7.P$1, U14.5
unnamed: I2C6.3, R25.2
unnamed: I2C6.1, R26.2
unnamed: A14.2, R31.1
unnamed: A15.2, R32.1
unnamed: D8.C, R31.2, R32.2
unnamed: L8.P$1, U16.5
unnamed: I2C7.3, R29.2
unnamed: I2C7.1, R30.2
unnamed: A16.2, R35.1
unnamed: A17.2, R36.1
unnamed: D9.C, R35.2, R36.2
unnamed: L9.P$1, U18.5
unnamed: I2C8.3, R33.2
unnamed: I2C8.1, R34.2
unnamed: A18.2, R39.1
unnamed: A19.2, R40.1
unnamed: D10.C, R39.2, R40.2
unnamed: L10.P$1, U20.5
unnamed: I2C9.3, R37.2
unnamed: I2C9.1, R38.2
unnamed: A20.2, R43.1
unnamed: A21.2, R44.1
unnamed: D11.C, R43.2, R44.2
unnamed: L11.P$1, U22.5
unnamed: I2C10.3, R41.2
unnamed: I2C10.1, R42.2
unnamed: A22.2, R47.1
unnamed: A23.2, R48.1
unnamed: D12.C, R47.2, R48.2
unnamed: L12.P$1, U24.5
unnamed: I2C11.3, R45.2
unnamed: I2C11.1, R46.2
unnamed: A24.2, R51.1
unnamed: A25.2, R52.1
unnamed: D13.C, R51.2, R52.2
unnamed: L13.P$1, U26.5
unnamed: I2C12.3, R49.2
unnamed: I2C12.1, R50.2
unnamed: A26.2, R55.1
unnamed: A27.2, R56.1
unnamed: D14.C, R55.2, R56.2
unnamed: L14.P$1, U28.5
unnamed: I2C13.3, R53.2
unnamed: I2C13.1, R54.2
unnamed: A28.2, R59.1
unnamed: A29.2, R60.1
unnamed: D15.C, R59.2, R60.2
unnamed: L15.P$1, U30.5
unnamed: I2C14.3, R57.2
unnamed: I2C14.1, R58.2
unnamed: A30.2, R63.1
unnamed: A31.2, R64.1
unnamed: D16.C, R63.2, R64.2
unnamed: L16.P$1, U32.5
unnamed: I2C15.3, R61.2
unnamed: I2C15.1, R62.2
unnamed: A32.2, R67.1
unnamed: A33.2, R68.1
unnamed: D17.C, R67.2, R68.2
unnamed: L17.P$1, U34.5
unnamed: I2C16.3, R65.2
unnamed: I2C16.1, R66.2
unnamed: A34.2, R71.1
unnamed: A35.2, R72.1
unnamed: D18.C, R71.2, R72.2
unnamed: L18.P$1, U36.5
unnamed: I2C17.3, R69.2
unnamed: I2C17.1, R70.2
SCL: IC1.22, J3.4, J4.4, J5.4, R5.1
SCL1: IC2.22, J1.4, J2.4, J6.4, R6.1
SCL2: IC3.22, J7.4, J8.4, J9.4, R10.1
SCL3: IC4.22, J10.4, J11.4, J12.4, R14.1
SCL4: IC5.22, J13.4, J14.4, J15.4, R18.1
SCL5: IC6.22, J16.4, J17.4, J18.4, R22.1
SCL6: IC7.22, J19.4, J20.4, J21.4, R26.1
SCL7: IC8.22, J22.4, J23.4, J24.4, R30.1
SCL8: IC9.22, J25.4, J26.4, J27.4, R34.1
SCL9: IC10.22, J28.4, J29.4, J30.4, R38.1
SCL10: IC11.22, J31.4, J32.4, J33.4, R42.1
SCL11: IC12.22, J34.4, J35.4, J36.4, R46.1
SCL12: IC13.22, J37.4, J38.4, J39.4, R50.1
SCL13: IC14.22, J40.4, J41.4, J42.4, R54.1
SCL14: IC15.22, J43.4, J44.4, J45.4, R58.1
SCL15: IC16.22, J46.4, J47.4, J48.4, R62.1
SCL16: IC17.22, J49.4, J50.4, J51.4, R66.1
SCL17: IC18.22, J52.4, J53.4, J54.4, R70.1
SDA: IC1.23, J3.3, J4.3, J5.3, R4.1
SDA1: IC2.23, J1.3, J2.3, J6.3, R1.1
SDA2: IC3.23, J7.3, J8.3, J9.3, R9.1
SDA3: IC4.23, J10.3, J11.3, J12.3, R13.1
SDA4: IC5.23, J13.3, J14.3, J15.3, R17.1
SDA5: IC6.23, J16.3, J17.3, J18.3, R21.1
SDA6: IC7.23, J19.3, J20.3, J21.3, R25.1
SDA7: IC8.23, J22.3, J23.3, J24.3, R29.1
SDA8: IC9.23, J25.3, J26.3, J27.3, R33.1
SDA9: IC10.23, J28.3, J29.3, J30.3, R37.1
SDA10: IC11.23, J31.3, J32.3, J33.3, R41.1
SDA11: IC12.23, J34.3, J35.3, J36.3, R45.1
SDA12: IC13.23, J37.3, J38.3, J39.3, R49.1
SDA13: IC14.23, J40.3, J41.3, J42.3, R53.1
SDA14: IC15.23, J43.3, J44.3, J45.3, R57.1
SDA15: IC16.23, J46.3, J47.3, J48.3, R61.1
SDA16: IC17.23, J49.3, J50.3, J51.3, R65.1
SDA17: IC18.23, J52.3, J53.3, J54.3, R69.1

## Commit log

2021-07-14 Add LED datasheets
2021-07-21 Update design for protos
    Add 5V boost circuit for ht16k33
2021-07-21 Run schematic/board autochecklist
    Update font to vector
    Make sure all parts (except for new ones) are in SF Eagle libs
    Add measures
2021-07-26 Updates after proto review
    Update HT16K33 to VK16K33
    Compared datasheets, it’s a drop in replacement!
    Removed PWR LED and jumper
    5V net now connects to the LED driver IC
    New mounting hole design
    I2C pullups became 4.7k and removed jumper
2021-07-26 Re-generate buzzard labels
2021-07-26 Run checklist
    Add voltage ranges on schematic
2021-07-26 Fix mounting hole connections and add some extra dimensions
2021-07-26 Add prod_id to new LED mapping IC
2021-07-26 Update mounting hole placement and measures
2021-07-26 Generate gerbers
2021-07-27 Re-CAM
2021-08-18 Added test point to 5V rail
2021-08-18 Remove the 5V test point after all!
2021-08-31 Pete's design updates
    * Update address table with "open" and "closed"
    * Move address resistors and jumpers
2021-08-31 Pete's updates
    * Some silk updates: default address and address jumper labels
    * Bump version number v01 --> v10
2021-08-31 Updates from Review:
    * Mirrored J3 on sch
    * Updated via size so that they're all the same
    * Added GND vias near qwiic connectors
    * Flipped C1, re-routed
    * Moved SDA trace so that copper would flow in dead space (bottom)
    * Added I2C jumper and changed pull up resistors to 0402, 1K
2021-09-02 QC Double-check updates
    * Updated footprint of silsmart display so that pin 1 indicator was in the right place
    * Moved fiducials
2021-09-02 Change pullups from 1k to 4.7k
2021-09-03 Panelize
2021-09-03 Create new zip file of eagle files
2021-10-14 Removing extraneous files
    Removing extraneous files

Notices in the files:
parts and their libraries:
SparkFun-Capacitors: Licensing: Creative Commons ShareAlike 4.0 International - https://creativecommons.org/licenses/by-sa/4.0
SparkFun-Aesthetics: Released under the Creative Commons Attribution Share-Alike 4.0 License
SparkFun-Aesthetics: https://creativecommons.org/licenses/by-sa/4.0
